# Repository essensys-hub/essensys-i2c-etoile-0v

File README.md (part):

# essensys-i2c-etoile-0v – carte N2 « étoile 0 V » sur rail DIN

Carte qui relie le boîtier principal (BP, carte SC944D) aux boîtiers auxiliaires (BA1 SC940D, BA2 SC941C,
BA3 SC942C) d'une installation Essensys **en étoile** autour d'un plan 0 V commun, à la place du chaînage d'origine.
Depuis la révision B, elle porte aussi un module ESP32 qui écoute le bus sans pouvoir y émettre, surveille ses
tensions, horodate les surtensions et gère une alarme intrusion sur batterie (voir [Révision B](#révision-b--module-esp32-espion-et-alarme)).

## Contexte : foudre 2026

Un coup de foudre indirect (août 2026) a détruit des étages I2C entre le BP et les BA : la surtension induite fait
circuler un courant d'équilibrage dans le 0 V du chaînage BP → BA1 → BA2 → BA3, et les écrêteurs des lignes SDA/SCL
conduisent dès que la chute de tension sur ce 0 V devient trop forte. Analyse et retour d'expérience :
[synthèse RETEX foudre 2026](https://www.essensys.fr/docs/retex/foudre-2026/synthese/).

N2 est la mesure « court terme » côté câblage : raccourcir et doubler les chemins 0 V, isoler chaque BA (cavalier, PTC, TVS).

- Change OpenSpec : [`i2c-surge-protection-2026-10-007`](https://github.com/essensys-hub/essensys-board-SC944D/tree/feat/i2c-surge-protection-2026-10-007/openspec/changes/i2c-surge-protection-2026-10-007)
  dans essensys-board-SC944D, tâche 4.1 (sections D3/D4 de `design.md`, spec `aux-box-interconnect`).
- Ticket : [essensys-hub/essensys-board-SC944D#1](https://github.com/essensys-hub/essensys-board-SC944D/issues/1).

## Fonction

N2 remplace le chaînage BP → BA1 → BA2 → BA3 par une **étoile** : le bus du BP (J31) arrive sur la carte
et repart vers chaque BA par un port dédié. Le 0 V de chaque BA rejoint celui du BP par un **plan 0 V double face**,
avec deux faisceaux AWG20 par BA (J1 et J2 du BA). Le 0 V du BP est doublé par une queue de cochon AWG20
soudée sur la broche traversante J31-3. But : relever le seuil de courant d'équilibrage à partir duquel
les écrêteurs I2C conduisent (au moins 4 fois la référence, à mesurer en 4.3), et garder l'écart statique de 0 V
sous 0,05 V.

Par port BA :

- **cavalier JPn** (embase 2×3 au pas de 2,54 mm, 3 shunts) qui coupe SDA, SCL et +15 V ; le 0 V n'est jamais coupé.
  Un pont 2×3 (boîtier femelle 2×3 avec 3 boucles) permet d'ouvrir les trois lignes en une seule manœuvre ;
- **PTC Fn** (CMS 1812, 30 V au moins) sur le +15 V, **puis TVS Dn SMAJ16A** entre le +15 V du port et le 0 V.
  Une TVS en court-circuit ne fait déclencher que la PTC de son port : les autres BA restent alimentés.

Partie bus : aucun composant actif, aucun firmware, aucune retouche des BA.

## Brochage (WR-MPC3 2×2, compatible Würth 66200421122)

| Broche | Signal |
|---|---|
| 1 | SDA |
| 2 | SCL |
| 3 | 0 V |
| 4 | +15 V |

| Repère | Rôle |
|---|---|
| J1 | Entrée BP, vers J31 du BP |
| J8 | Pastille (Ø 1,25 mm) pour la queue de cochon AWG20 vers J31-3 du BP |
| J2 / J3 | BA1 SC940D, vers J1 / J2 du BA |
| J4 / J5 | BA2 SC941C, vers J1 / J2 du BA |
| J6 / J7 | BA3 SC942C, vers J1 / J2 du BA |
| JP1 / JP2 / JP3 | Cavalier du port BA1 / BA2 / BA3 (impairs côté BP, pairs côté port) |
| F1–F3, D1–D3 | PTC puis TVS du +15 V de chaque port |
| H1–H4 | Trous M3 non métallisés, **non reliés** (fixation sur support DIN isolant) |

Nets : `SDA_BP`, `SCL_BP`, `+15V_BP`, `0V` ; par port `SDA_BAn`, `SCL_BAn`, `+15V_SWn` (après cavalier), `+15V_BAn` (après PTC).

## Carte

- **235 × 68 mm** (révision B ; zone bus 110 mm à gauche, zone module à droite), FR-4 1,6 mm, 2 couches,
  **cuivre 2 oz (70 µm) demandé**, HASL, vernis vert, sérigraphie blanche. Six trous M3 non reliés.
- Plan 0 V sur les deux faces (raccord plein, sans thermique), vias de couture, liaison J31-3 → pastille J8 en piste de 3 mm.
- Pistes : +15 V 1,5 à 2 mm, SDA/SCL 0,5 mm ; tronc en peigne depuis J1, une descente par port.
- Support DIN : à monter sur un porte-carte DIN **isolant** (profilé plastique pour carte de 68 mm, ou entretoises nylon M3 sur adaptateur DIN). Les trous de fixation ne sont reliés à rien.
- Zone module : plan GND sur les deux faces, vias de couture, zone sans cuivre sous l'antenne de l'ESP32 (bord haut).
  Pistes 0,25 mm (signaux), 0,4 mm (3,3 V) et 0,6 mm (puissance), vias 0,6/0,3 mm, isolement 0,2 mm.

## Révision B : module ESP32 espion et alarme

Change OpenSpec [`n2-esp32-spy-alarm-2026-10-008`](openspec/changes/n2-esp32-spy-alarm-2026-10-008),
ticket [essensys-hub/essensys-feature-lifecycle#28](https://github.com/essensys-hub/essensys-feature-lifecycle/issues/28).
Tâches matérielles couvertes ici : 1.1, 1.2, 1.3 (conception), 2.1 et 2.2 (conception, essais sur banc à faire).
Le firmware est dans `firmware/` (autre lot du même change).

La révision B ajoute à droite de la carte une **zone module** qui observe le bus sans pouvoir agir dessus,
surveille ses tensions, horodate les surtensions et gère une alarme intrusion sur batterie.
La zone bus (révision A, à gauche) est inchangée : seuls s'y ajoutent les prises de mesure, le cavalier d'écoute
et l'alimentation de l'isolateur.

### Séparation bus / module

- Deux plans distincts : **0 V** (zone bus, x < 110,3 mm) et **GND** (zone module, x > 111,7 mm), séparés par un sillon
  de 1,4 mm repéré en sérigraphie. GND rejoint le 0 V **en un seul point**, par le net-tie NT1.
- Rien n'est relié au PE : trous M3 non métallisés, aucune borne de terre. La sérigraphie TBTS est conservée
  sur les deux faces (« 0 V TBTS – NE PAS RELIER À LA TERRE », « ZONE MODULE (GND) – TBTS – AUCUNE LIAISON AU PE »).
- Seuls traversent le sillon (vérifié sur le PCB routé) : l'isolateur U1 (à cheval), NT1, le +15V_BP vers la PTC
  propre F4 du module, et les 13 lignes de mesure (MEAS_*, DA_*) **déjà limitées en courant** par leur résistance
  de prise, placée côté bus au plus près du point mesuré (150 kΩ pour les +15 V, 100 kΩ pour les prises Kelvin 0 V).

### Composants retenus

| Fonction | Repères | Référence | Remarque |
|---|---|---|---|
| MCU Wi-Fi | U6 | ESP32-C3-MINI-1-N4 | Antenne en bord de carte, zone interdite cuivre de 43 × 6,4 mm (D1) |
| Isolateur d'écoute | U1 | **ISO7720DR** (TI), 2 canaux **même sens** | Seconde source broche à broche : ADuM1200ARZ (2/0) |
| LDO côté bus de l'isolateur | U2, R3 | LP2950-5.0 (TO-92, VIN 30 V) + 100 Ω | Alimenté par +15V_BP, indépendant du module |
| Cavalier d'écoute | JP4 | Embase 2×2, 2 shunts | Retirés : aucune liaison module ↔ SDA/SCL |
| RTC | U7, C20 | RV-3028-C7 (I2C 0x52) + supercondensateur 11 mF (CPH3225A) | EVI relié au latch 0 V : horodatage matériel |
| ADC | U10–U13 | 4 × MCP3428 (16 bits, réf. interne 2,048 V, entrées différentielles) | Bus I2C local du module |
| Amplis différentiels | U9 | TLV9064 (RRIO, 10 MHz) | 3 canaux G = 0,249 + tampon VREF |
| Latch surtension | U14, U15, U16 | 2 × LM339 + 74HC74 | Réarmé par GPIO7 |
| Extension d'E/S | U8 | TCA9534 (I2C 0x20) | Latches, chargeur, clé, secteur, LED |
| PTC propre, anti-retour, TVS | F4, D4, D5 | PTC 1812 0,2 A, SS14, SMAJ16A | Défaut du module = F4 ouverte, BA alimentés |
| Abaisseur 15 → 5 V | U3, L1 | AP63205WU (5 V fixe, 3,8–32 V) + 4,7 µH | |
| Chargeur LiFePO4 | U4, TH1 | CN3058E (CC/CV 3,6 V), RISET 9,1 kΩ = 200 mA, CTN 10 kΩ B3435 | Charge autorisée ≈ 3–43 °C |
| Power-path | D6, Q1 | SS14 (secteur) + AO3401A (batterie) | Basculement sans coupure par la diode de structure de Q1 |
| LDO 3,3 V | U5 | AP2112K-3.3 | |
| Batterie | BT1, F5 | Porte-pile Keystone 1042 + IFR18650 1,5 Ah, PTC 1,5 A | |
| Entrées alarme | J10, R71–R78, D11–D14 | 4 boucles équilibrées, 1 kΩ série, SMF5.0A | FDL 2 × 4,7 kΩ |
| Clé d'armement | J11, R79, R80, D15 | Contact sec | |
| Sirène 12 V | U17, L2, D7, U18, D16 | MT3608 (boost 12 V depuis VBAT) + **BTS4140N** (high-side protégé) | Boost et sortie coupés au reset |

**Choix de l'isolateur.** L'ISO7721 et l'ADuM1201 ont un canal dans chaque sens : leur canal retour piloterait
une sortie côté bus, exactement ce que la spec interdit. Ils ne conviendraient qu'en n'utilisant qu'un canal
par boîtier (deux boîtiers, un canal retour inutilisé mais physiquement présent). L'**ISO7720** a ses deux canaux
dans le sens bus → module : côté bus il n'existe que des **entrées CMOS** (≈ 2 pF, fuite typique de quelques nA,
10 µA max en datasheet), aucune sortie. Aucune configuration logicielle ne peut donc tirer SDA ou SCL. Sa sortie
est « fail-safe haute » (niveau repos d'I2C). Le côté bus est alimenté en 5 V (niveau du bus du BP) par U2,
ce qui garde les entrées dans leur plage même quand le module est éteint.

### Raccordement firmware (ESP32-C3)

| GPIO | Net | Rôle |
|---|---|---|
| 0 | SNF_SCL | Écoute SCL (sortie OUTB de l'isolateur), entrée seule |
| 1 | SNF_SDA | Écoute SDA (OUTA), entrée seule |
| 2 | IO2 | Broche de démarrage, tirage haut 10 kΩ, libre |
| 3 | EXP_INT | /INT du TCA9534 (réveil possible) |
| 4 / 5 | I2C_SDA / I2C_SCL | Bus I2C **local** du module (4,7 kΩ), distinct du bus espionné |
| 6 | SIREN_EN | Active le boost et la sortie sirène (tirage bas 100 kΩ) |
| 7 | LATCH_RST | Réarmement des latches, actif bas (tirage haut 10 kΩ) |
| 8 | LED_STAT | LED verte, active basse (broche de démarrage, tirage haut) |
| 9 | BOOT | Bouton SW1 (démarrage / service) |
| 10 | RTC_INT | /INT du RV-3028 |
| 18 / 19 | USB_DM / USB_DP | Débogage USB (J9) |
| 20 / 21 | U0RX / U0TX | Débogage UART (J9) |

TCA9534 (0x20) : P0 LATCH_0V, P1 LATCH_OV, P2 /CHRG, P3 /DONE, P4 ARM_IN (bas = clé fermée),
P5 PG_5V (haut = secteur présent), P6 LED rouge (active basse), P7 libre (tirée bas).

MCP3428 (adresses selon la table de la datasheet, à confirmer par un scan I2C au banc, plage 0x68–0x6F) :

| Repère | Adr0 / Adr1 | CH1 | CH2 | CH3 | CH4 |
|---|---|---|---|---|---|
| U10 | 0 / 0 | +15V_BP | +15V_SW1 (amont PTC F1) | +15V_SW2 | +15V_SW3 |
| U11 | 1 / 0 | +15V_BA1 (aval PTC F1) | +15V_BA2 | +15V_BA3 | VBAT (÷ 2) |
| U12 | 0 / 1 | Boucle Z1 | Z2 | Z3 | Z4 |
| U13 | 1 / 1 | Écart 0 V port BA1 (CH− = VREF) | BA2 | BA3 | Sortie sirène (÷ 11) |

Le RV-3028 doit être configuré par le firmware : chargeur d'entretien (trickle) activé vers VBACKUP,
basculement automatique sur VBACKUP, entrée EVI sur front montant (horodatage du latch « écart de 0 V »).

### Tolérances des chaînes de mesure (tâche 1.2)

Hypothèses : résistances de mesure 0,1 % 25 ppm/°C, échauffement de 30 °C, MCP3428 à 15 éch./s
(16 bits, LSB 62,5 µV, erreur de gain 0,35 % max, offset 15 µV, réf. 15 ppm/°C), TLV9064 offset 1,6 mV max,
LM339 offset 5 mV max. « Pire cas » = somme des erreurs maximales ; « RSS » = somme quadratique.
La colonne « Résolution » suppose le mode 16 bits ; en 12 bits (240 éch./s, mode choisi par le firmware)
elle devient 16 mV sur les +15 V, 2 mV sur VBAT et 4 mV sur l'écart de 0 V, sans changer les erreurs de gain.

| Chaîne | Rapport, pleine échelle | Résolution | Pire cas | RSS | Remarque |
|---|---|---|---|---|---|
| +15 V amont/aval des PTC (7 canaux) | 10 k / (150 k + 10 k) = 1/16 ; 32,8 V | 1,0 mV | ± 0,72 % (± 0,11 V à 15 V) | ± 0,43 % (± 0,07 V) | Charge de l'ADC (2,25 MΩ) : − 0,42 % systématique, corrigée par le firmware ; sans correction ± 1,14 % (± 0,17 V) |
| VBAT | 1/2 ; 4,1 V | 0,13 mV | ± 0,9 % (± 32 mV à 3,6 V) | ± 0,6 % | Charge de l'ADC − 2,2 % systématique, corrigée ; seuil « batterie faible » 3,0 V |
| Écart de 0 V (3 canaux) | G = 24,9 k / 100 k = 0,249 ; − 4,0 V … + 8,2 V | 0,25 mV | ± (8 mV + 0,6 % de la lecture) | ± (4 mV + 0,4 %) | Offset dominé par le TLV9064 ; avec un zéro mesuré à la mise en service : ± (1 mV + 0,6 %). Objectif 4.3 (≤ 0,05 V) mesurable |
| Seuil du latch « écart de 0 V » | ± 1,00 V (fenêtre VREF ± 0,249 V) | – | ± 0,06 V | ± 0,03 V | Comparateurs ± 32 mV, ampli ± 8 mV, tampon VREF ± 6 mV, échelle ± 12 mV ; impulsion mini ≈ 1–2 µs (onde 8/20 µs captée) |
| Seuil du latch « surtension +15 V » | 16 × 1,249 V = 20,0 V | – | ± 0,15 V | ± 0,09 V | Filtre 9,4 kΩ / 100 pF (τ ≈ 0,9 µs) ; impulsion mini ≈ 2 µs |
| Boucles d'alarme | 3,3 V, 10 kΩ + 1 kΩ série | 0,06 mV | ± 4 % par état | – | FDL 5 %, 3,3 V ± 2 %, voir les seuils ci-dessous |
| Sortie sirène | 1/11 ; 22,5 V | 0,7 mV | ± 0,7 % | – | Détection de court-circuit (sortie < 6 V sirène active) |

Boucles équilibrées (FDL 4,7 kΩ en série avec le contact + 4,7 kΩ en parallèle) :

| État | Résistance de boucle | Tension mesurée | Seuils proposés |
|---|---|---|---|
| Court-circuit (sabotage) | 0 Ω | 0,30 V | < 0,75 V |
| Repos (fermée) | 4,7 kΩ | 1,20 V (1,15–1,25) | 0,75–1,44 V |
| Alarme (ouverte) | 9,4 kΩ | 1,68 V (1,61–1,75) | 1,44–1,95 V |
| Coupée (sabotage) | ∞ | saturation (≥ 2,047 V) | > 1,95 V |

Détection « PTC déclenchée » : aval < 2 V alors que l'amont est > 12 V (une PTC déclenchée laisse
quelques volts au plus). La chute normale dans une PTC (≈ 0,05 à 0,2 V) est du même ordre que l'erreur de deux
canaux : le module ne mesure pas le courant des départs, il détecte le déclenchement.

### Budget de consommation (calcul, mesure en tâche 2.3)

Charges du rail 3,3 V (moyennes) : ESP32-C3 Wi-Fi en économie et décodage I2C actif ≈ 40 mA (crête 350 mA
en émission), analogique et logique ≈ 7,8 mA (TLV9064 2,2 mA, 2 × LM339 1,6 mA, ISO7720 côté module
1,2 mA, 4 × MCP3428 0,6 mA, 4 boucles au repos 0,84 mA, LED 1,3 mA, échelle de seuils 0,1 mA).

| Cas (sur +15 V, rendement de l'abaisseur 85 %) | 5 V | +15 V |
|---|---|---|
| Batterie pleine, Wi-Fi en économie | 48 mA | 19 mA |
| **Batterie vide** (charge 200 mA) + Wi-Fi en économie | 248 mA | **97 mA** |
| Batterie vide + émission Wi-Fi (crête de quelques ms) | 560 mA | 220 mA |
| Côté bus : LP2950 + isolateur + 7 diviseurs de mesure | – | 2,3 mA |
| **Total pire cas en régime établi** | | **≈ 100 mA (1,5 W)** |

- La sirène est alimentée par **VBAT** (boost MT3608) et non par le +15 V : 12 V × 0,2 A ≈ 0,9 A sur la batterie
  pendant 3 min au plus (≈ 44 mAh), sans effet sur le +15 V du bus.
- F4 (Ihold 0,2 A à 23 °C, ≈ 0,16 A à 50 °C) tient les 100 mA établis ; les crêtes Wi-Fi de quelques ms
  ne la font pas déclencher (constante thermique de l'ordre de la seconde).
- Le +15 V du BP doit fournir ces ≈ 100 mA **en plus** des BA : à reporter dans le dimensionnement
  PTC ≥ 1,5 × BA_ALIM (design D7), vérification en 2.3.

Autonomie sur batterie (1,5 Ah, 80 % utilisables = 1,2 Ah ; sur batterie le BP a coupé le +15 V,
il n'y a plus de trafic I2C à décoder) :

| Profil firmware | Courant moyen | Autonomie |
|---|---|---|
| Wi-Fi actif en permanence (≈ 80 mA) | 88 mA | 14 h |
| Wi-Fi en économie, CPU actif (≈ 40 mA) | 48 mA | 25 h |
| Veille légère + DTIM, alarme armée (≈ 10 mA) | 18 mA | 67 h |

L'objectif de 24 h (tâche 5.4) suppose un firmware en économie d'énergie sur batterie (≤ 50 mA en moyenne).

## Fichiers

| Fichier | Contenu |
|---|---|
| `n2-etoile-0v.kicad_pro/.kicad_sch/.kicad_pcb` | Projet KiCad 9 |
| `n2-etoile-0v.kicad_sym`, `sym-lib-table`, `fp-lib-table` | Symboles propres (ESP32-C3-MINI-1, CN3058E) et tables de bibliothèques du projet |
| `export/n2-etoile-0v-schema.pdf` | Schéma |
| `export/n2-etoile-0v-bom.csv` | BOM |
| `export/n2-etoile-0v-gerber.zip` | Gerber, perçages Excellon, plan de perçage, job Gerber |
| `export/n2-etoile-0v-pcb-{top,bottom}.{png,svg}` | Rendus 3D et tracés cuivre |
| `rapports/erc.rpt`, `rapports/drc.rpt` | ERC et DRC (avec parité schéma) : 0 erreur, 0 avertissement |
| `scripts/` | Générateurs Python et `build.sh` : `n2_module.py` (composants et nets du module, source unique), `gen_sch.py`, `gen_pcb.py` (placement), `autoroute.py` (routeur maillé déterministe avec arrachage ciblé et réparation des plans), `fill_zones.py` |

## Régénérer

Prérequis : KiCad 9 installé dans `/Applications/KiCad` (macOS ; adapter `KC` et `KP` dans `scripts/build.sh` sinon).

```sh
sh scripts/build.sh
```

Le script régénère schéma et PCB (le routage du module prend environ 5 minutes), relance ERC et DRC
(avec parité schéma), refait tous les exports et échoue si ERC ou DRC signalent une erreur.
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
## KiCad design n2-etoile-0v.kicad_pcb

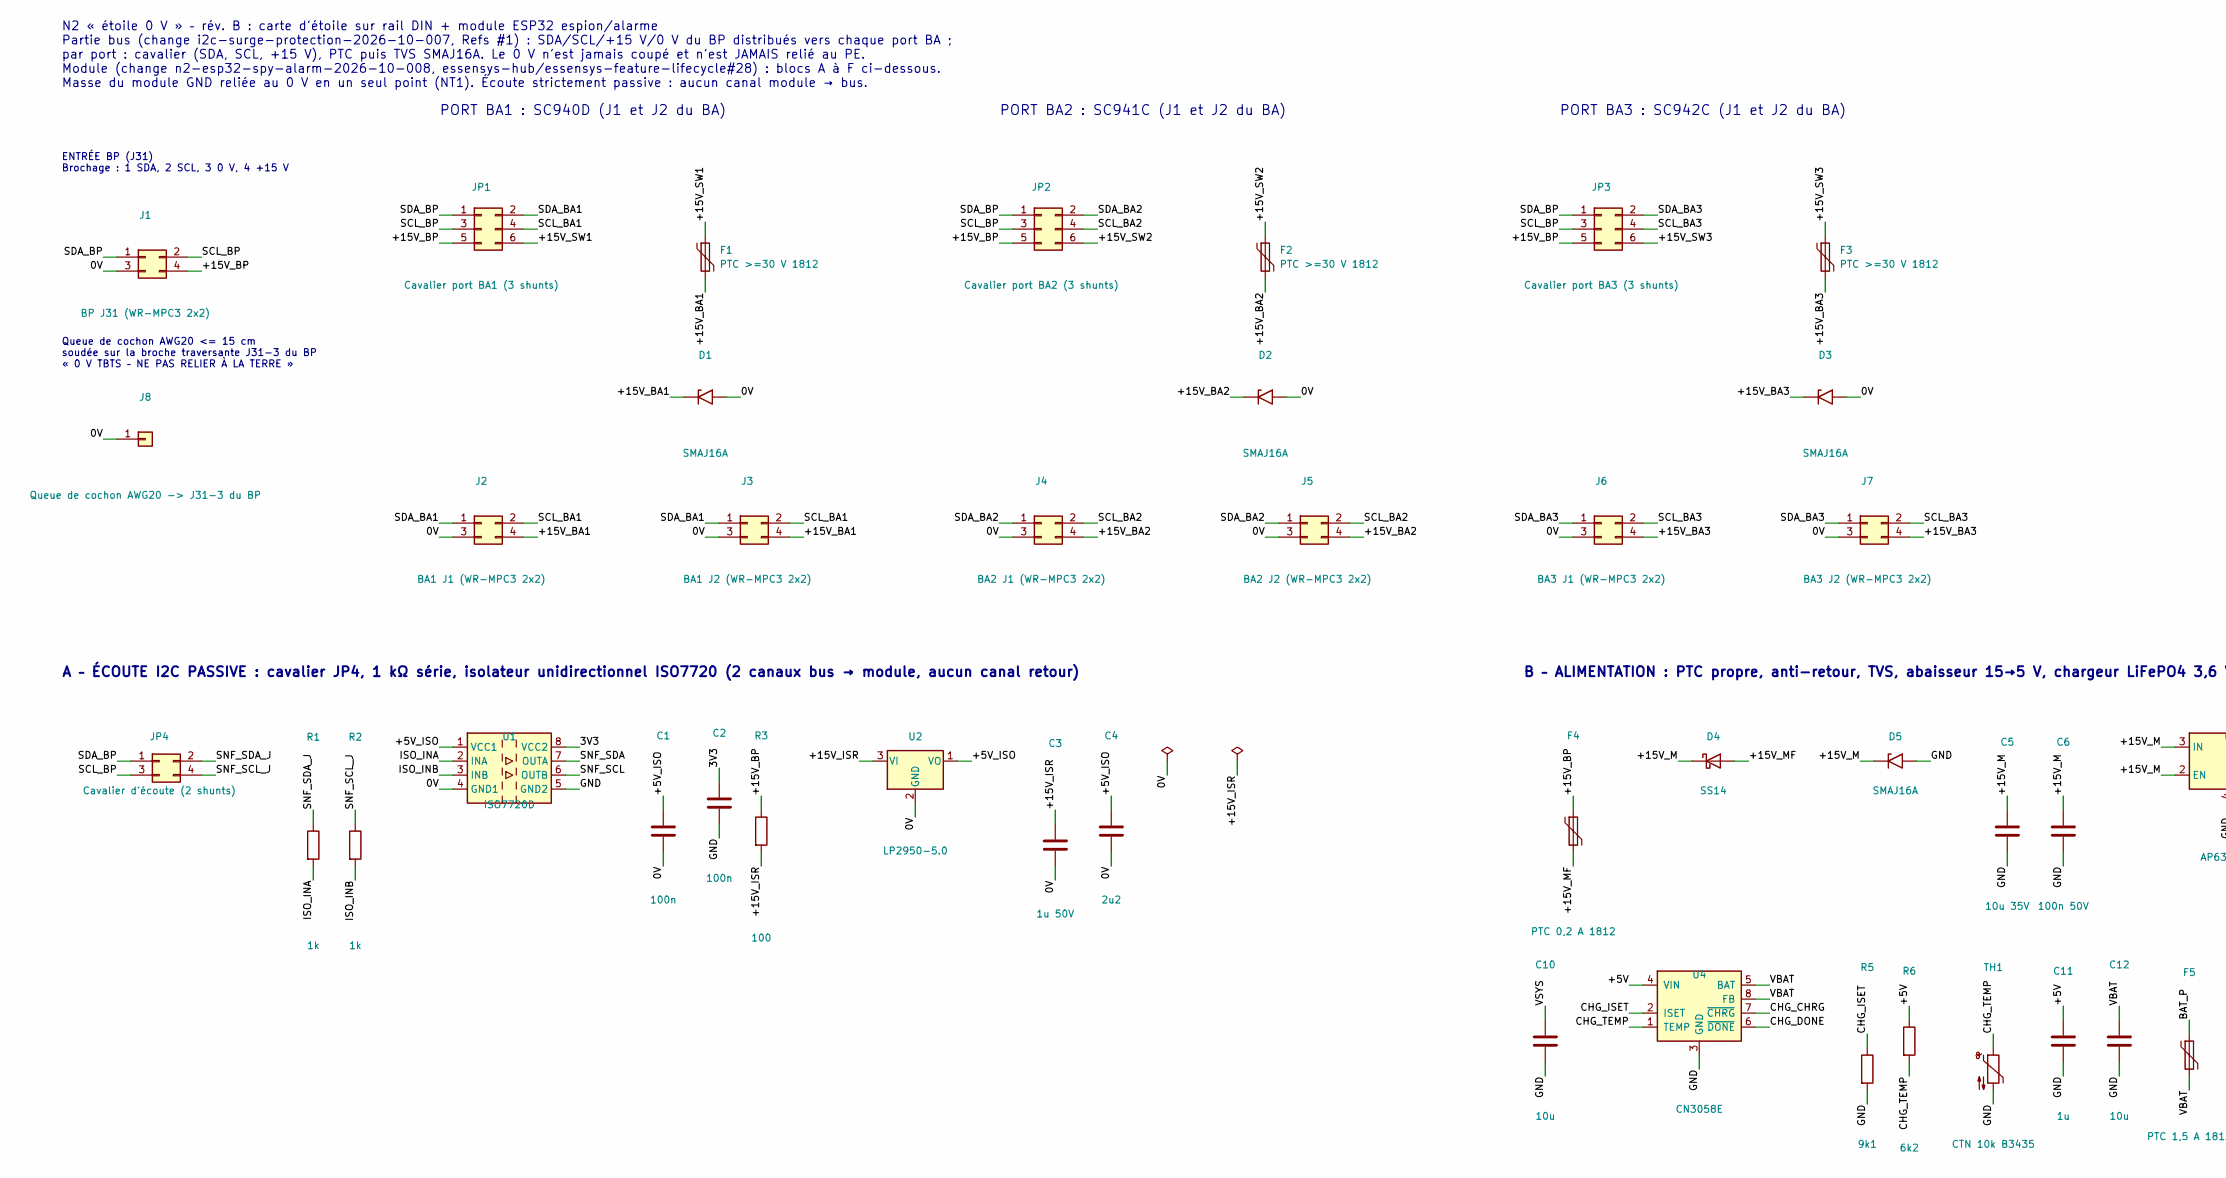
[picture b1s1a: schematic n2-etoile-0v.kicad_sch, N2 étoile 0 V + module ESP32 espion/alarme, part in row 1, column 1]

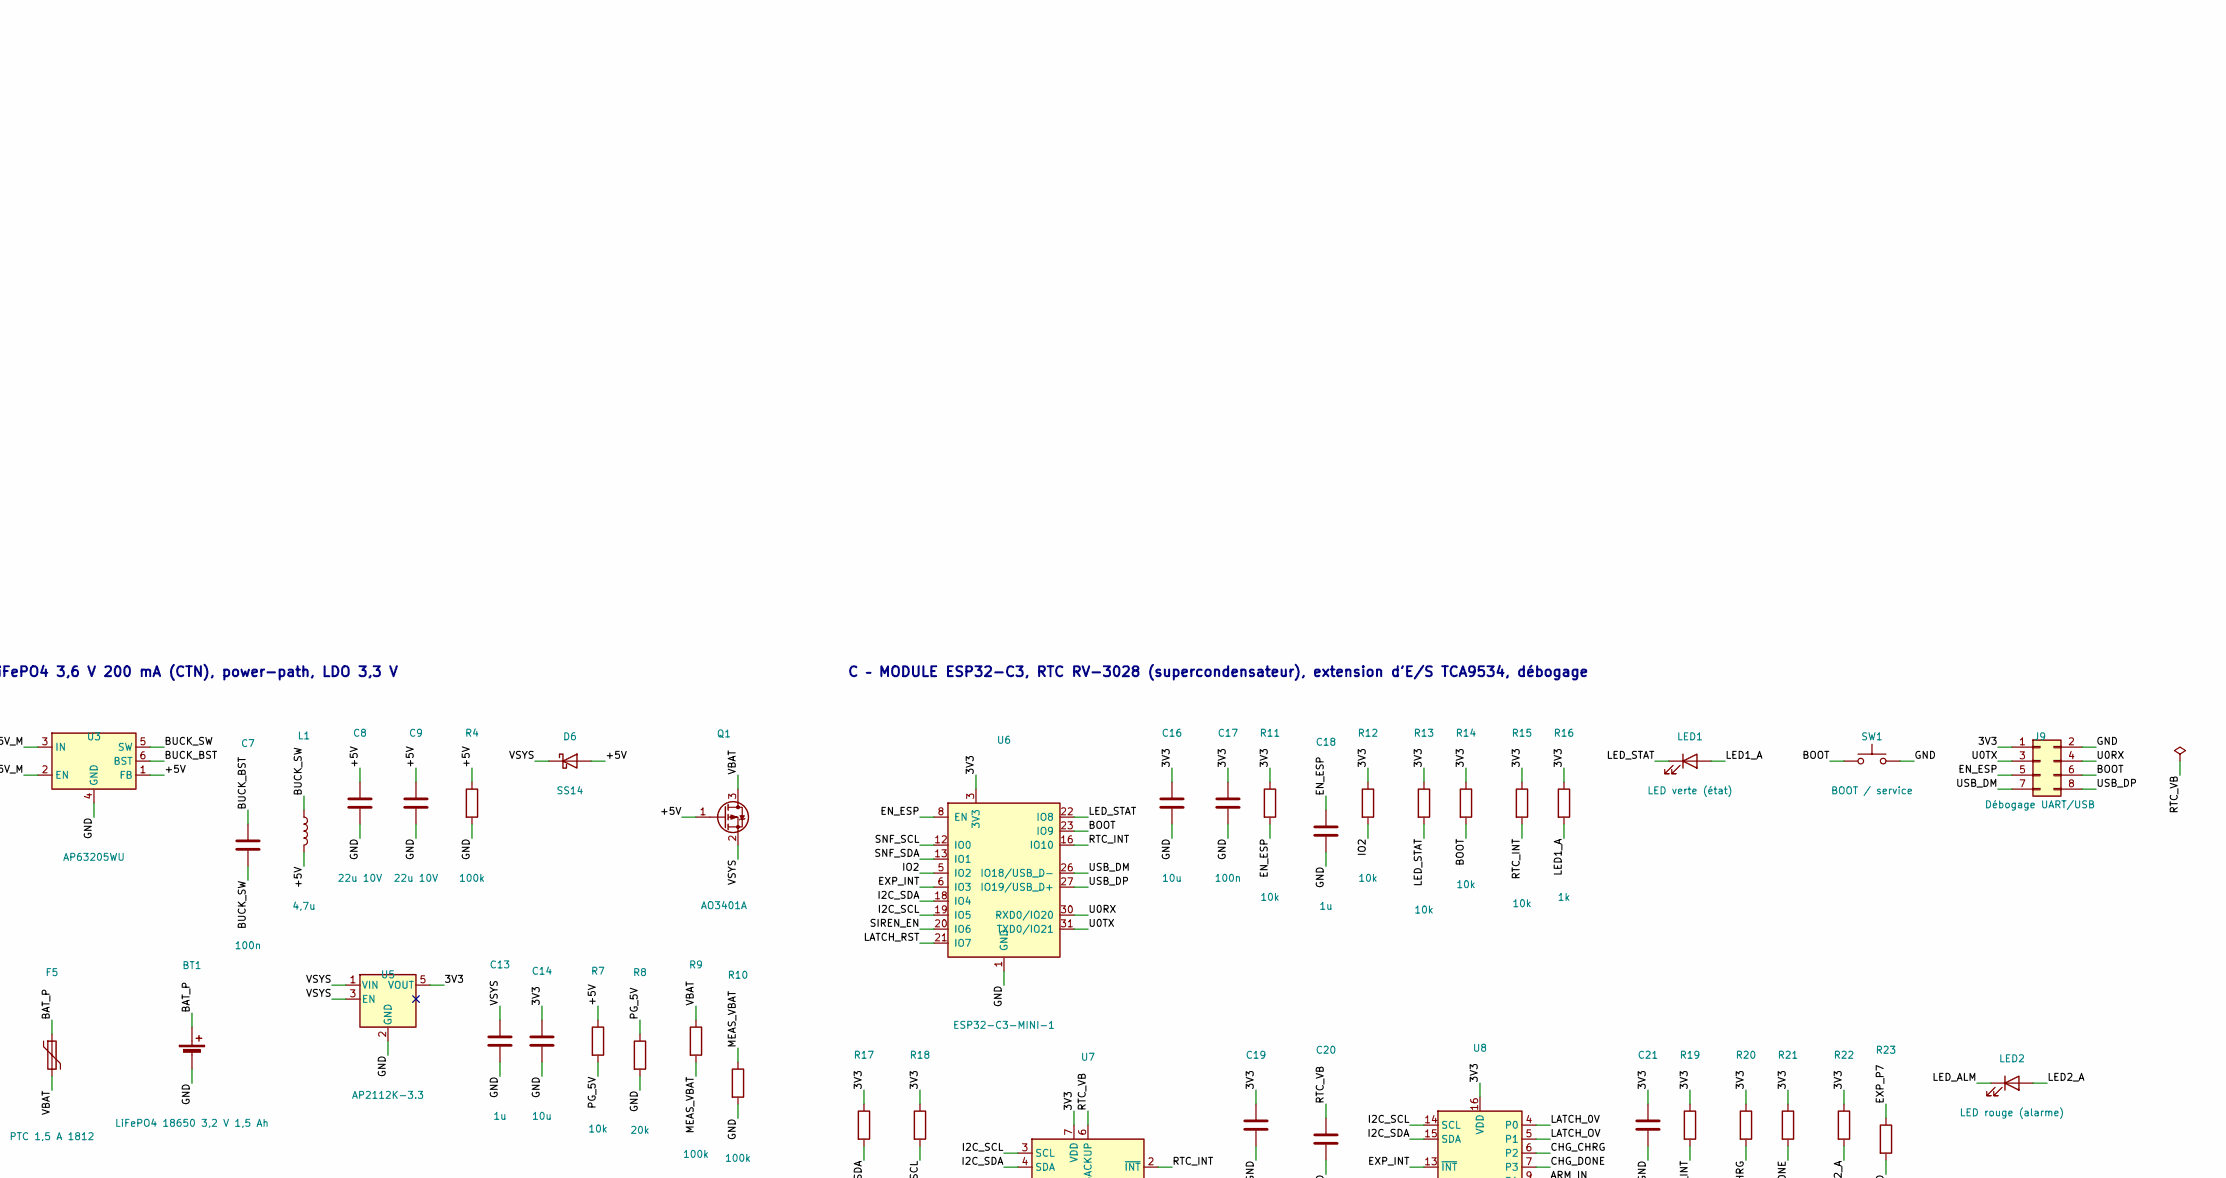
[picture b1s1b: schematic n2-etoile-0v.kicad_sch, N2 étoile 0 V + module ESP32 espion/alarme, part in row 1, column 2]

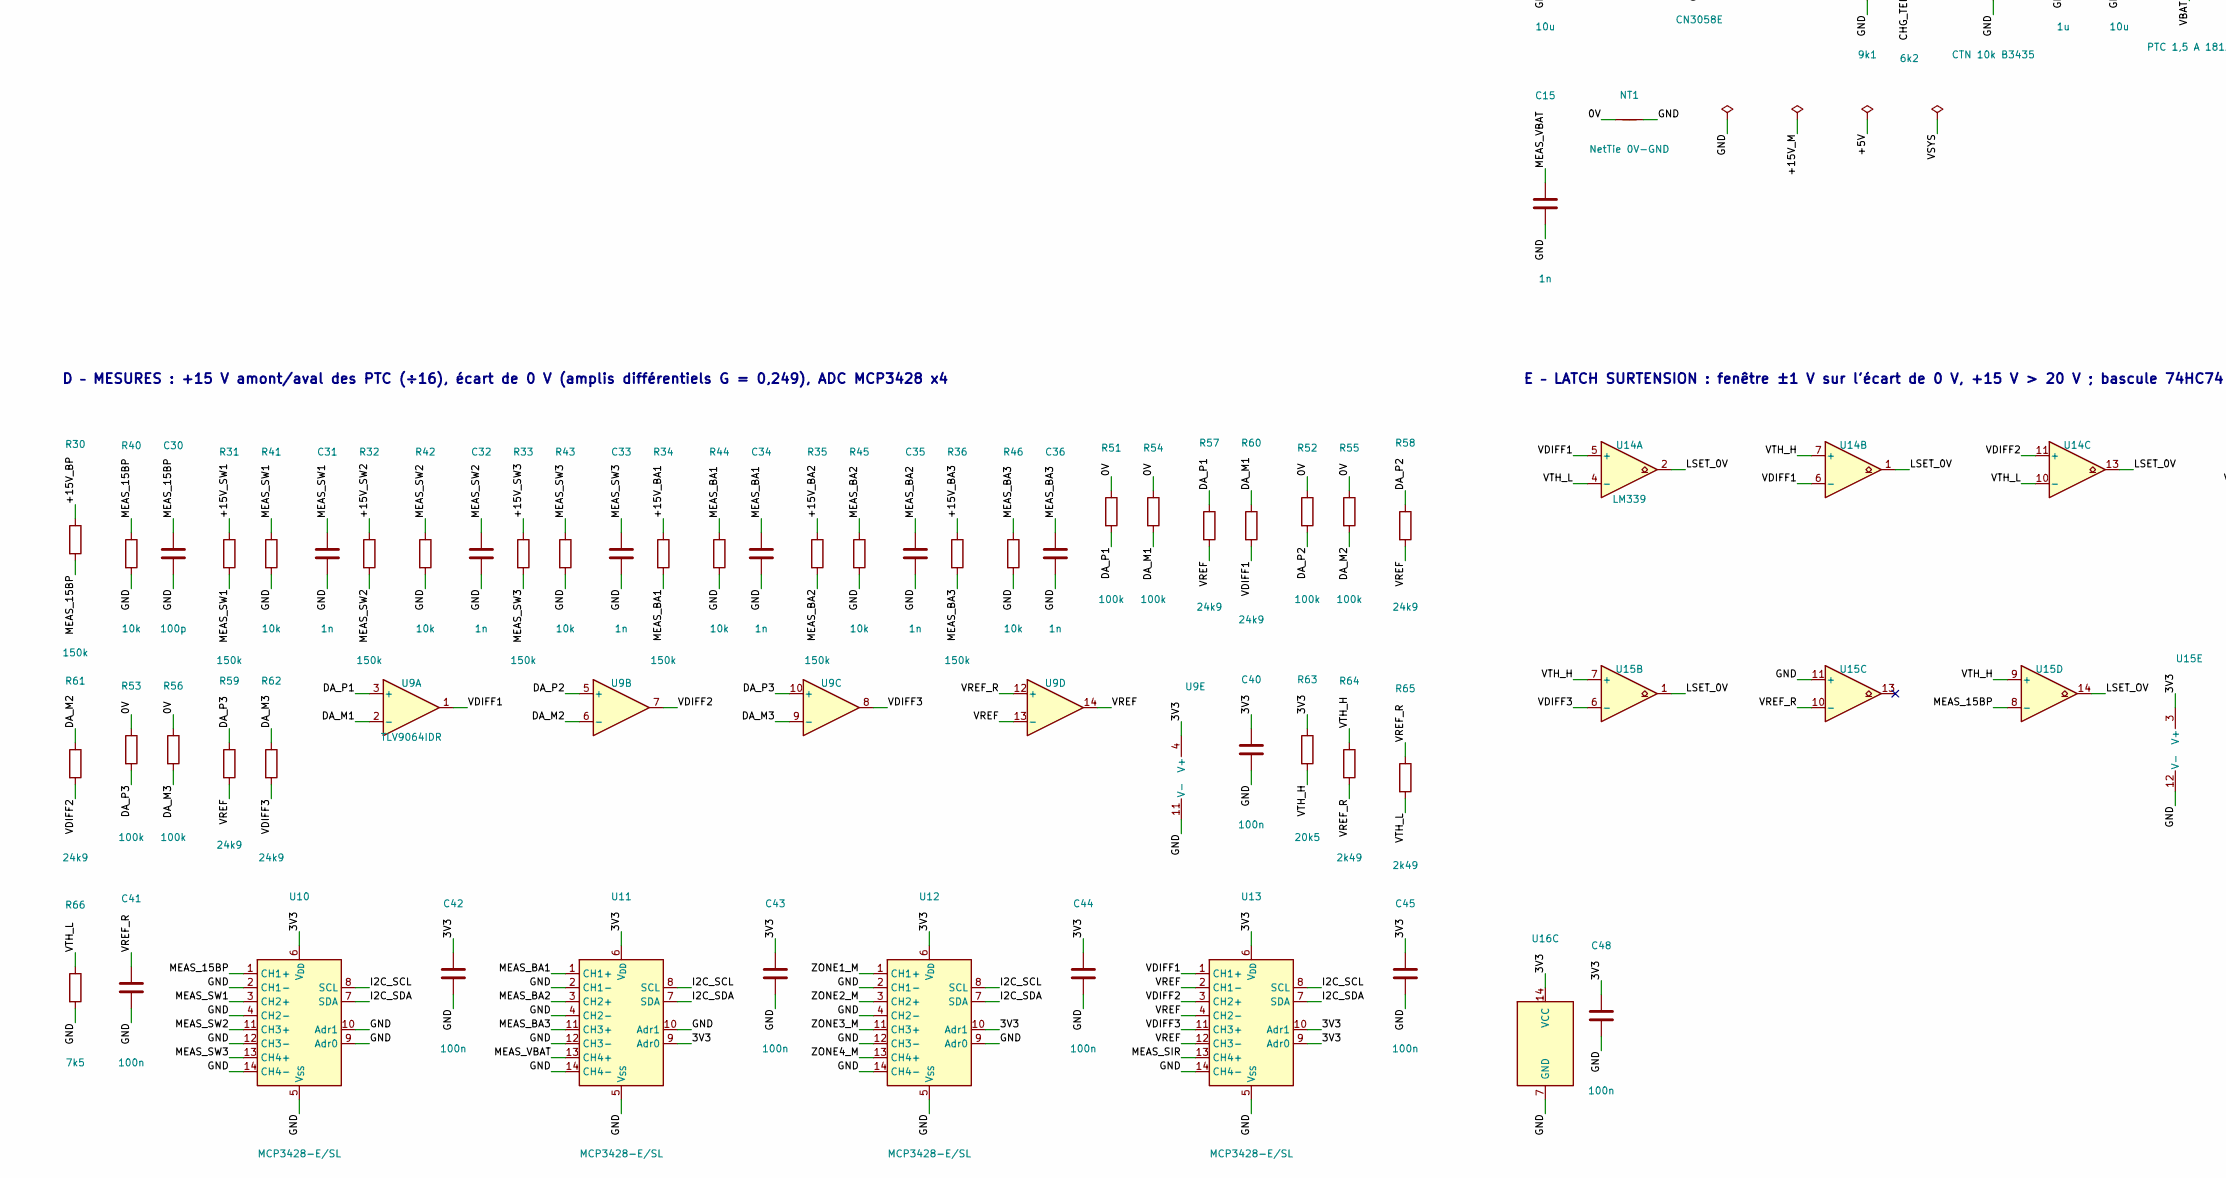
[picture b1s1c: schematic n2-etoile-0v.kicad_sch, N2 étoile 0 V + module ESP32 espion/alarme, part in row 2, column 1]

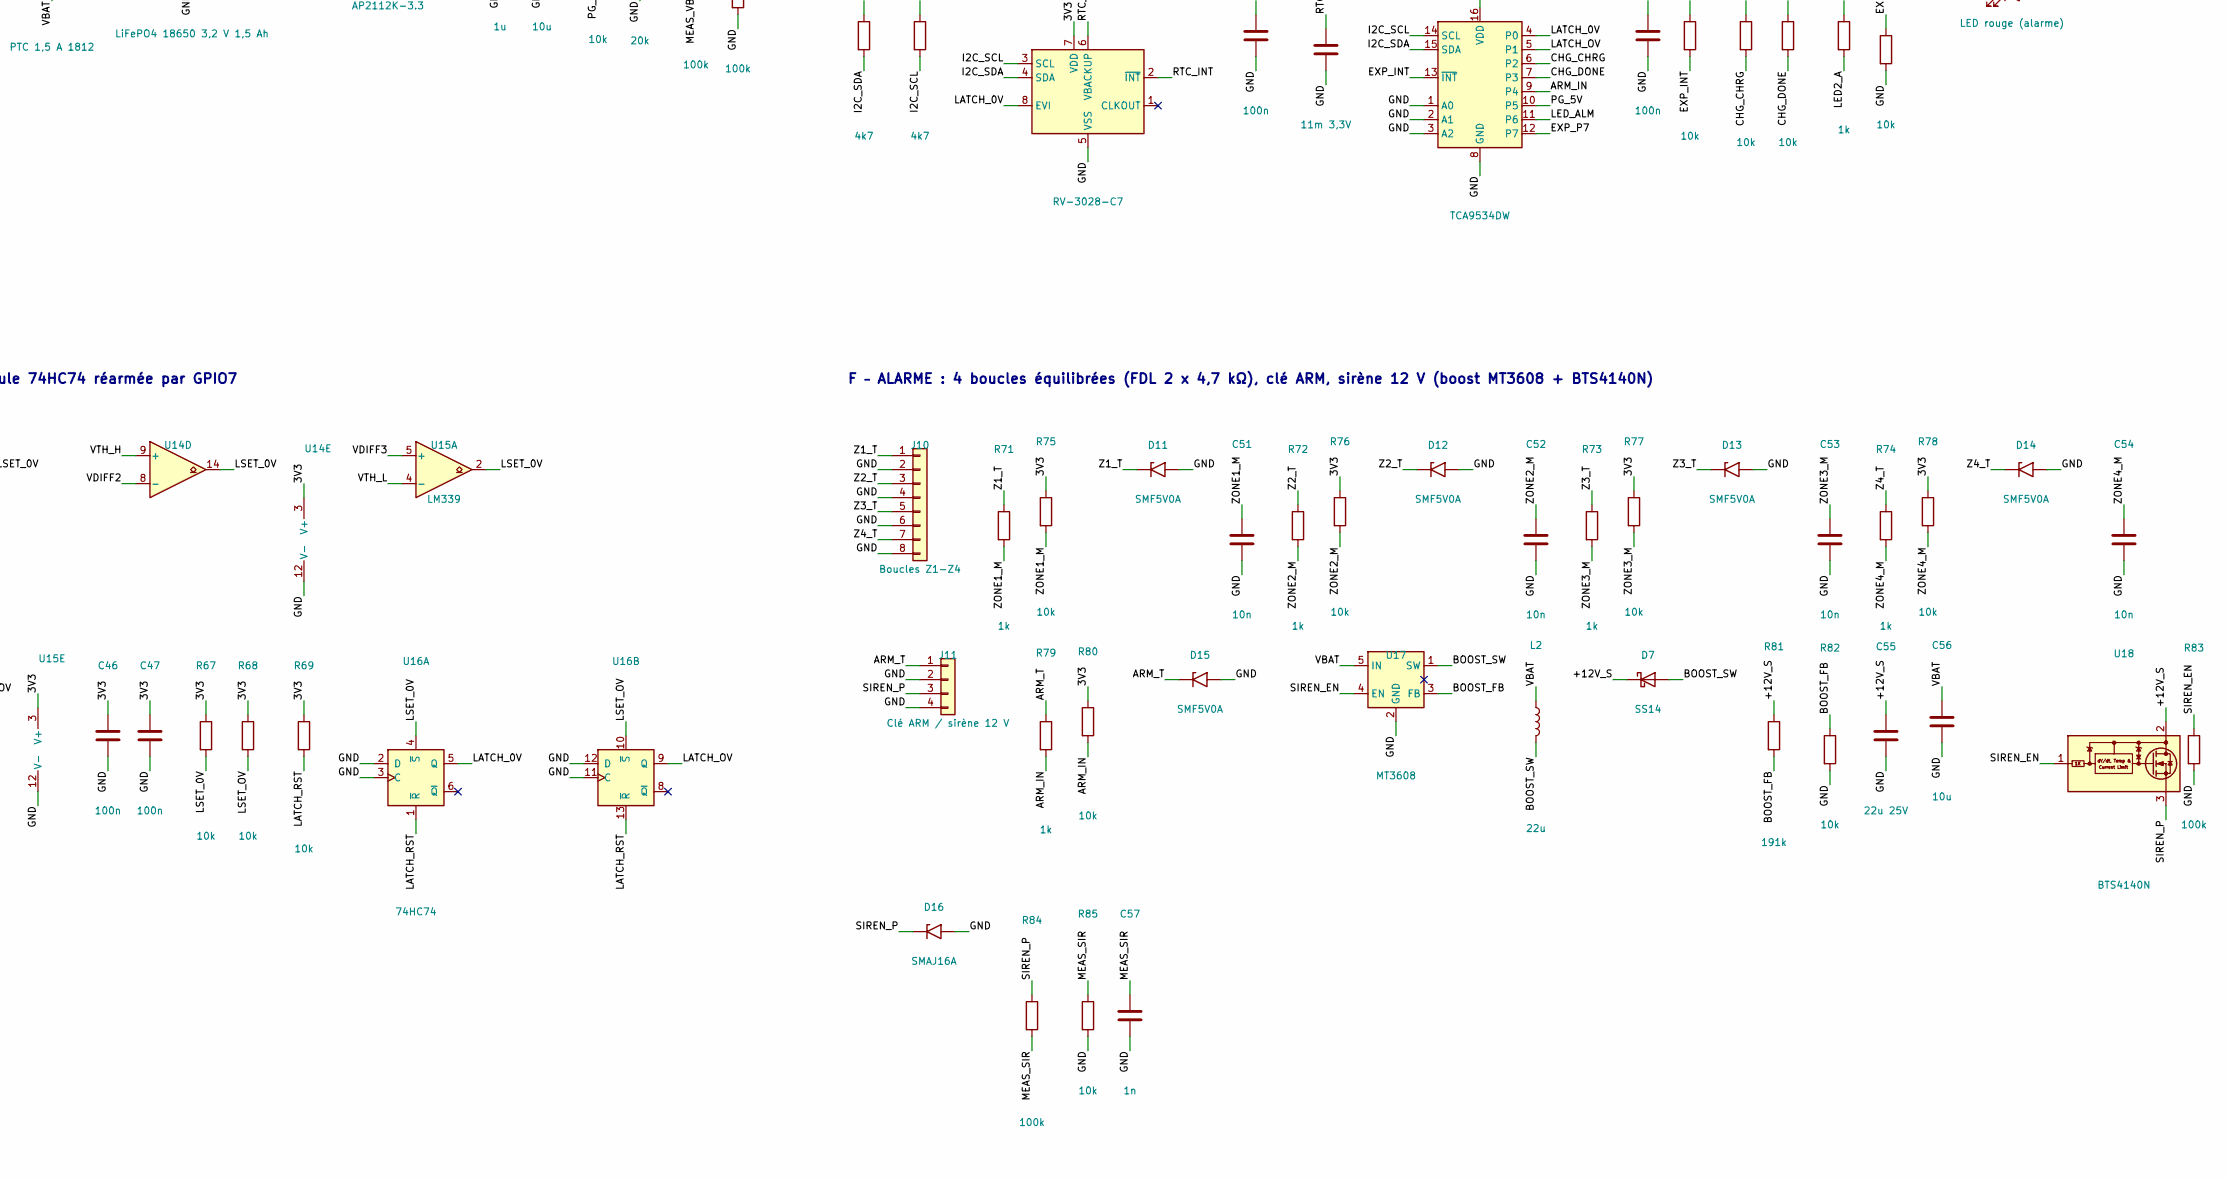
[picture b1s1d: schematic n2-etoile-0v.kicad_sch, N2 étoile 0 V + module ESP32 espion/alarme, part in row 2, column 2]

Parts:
BT1: LiFePO4 18650 3,2 V 1,5 Ah; BatteryHolder_Keystone_1042_1x18650; MPN 1042 (porte-pile 18650) + cellule IFR18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
C1, C2, C7, C17, C19, C21, C40, C41, C42, C43, C44, C45, C46, C47, C48: 100n; C_0603_1608Metric
C3: 1u 50V; C_0805_2012Metric
C4: 2u2; C_0603_1608Metric
C5: 10u 35V; C_1206_3216Metric
C6: 100n 50V; C_0603_1608Metric
C8, C9: 22u 10V; C_1206_3216Metric
C10, C12, C14, C16, C56: 10u; C_0805_2012Metric
C11, C13, C18: 1u; C_0603_1608Metric
C15, C31, C32, C33, C34, C35, C36, C57: 1n; C_0603_1608Metric
C20: 11m 3,3V; C_1210_3225Metric; MPN CPH3225A (supercondensateur, chargé par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
C30: 100p; C_0603_1608Metric
C51, C52, C53, C54: 10n; C_0603_1608Metric
C55: 22u 25V; C_1206_3216Metric
D1, D2, D3, D5, D16: SMAJ16A; D_SMA; MPN SMAJ16A
D4, D6, D7: SS14; D_SMA
D11, D12, D13, D14, D15: SMF5V0A; D_SMF; MPN SMF5.0A
F1, F2, F3: PTC >=30 V 1812; Fuse_1812_4532Metric; MPN 1812L050/30MR (à confirmer : Ihold@50°C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
F4: PTC 0,2 A 1812; Fuse_1812_4532Metric; MPN MF-MSMF020-2 (Ihold 0,2 A, 30 V, à conf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
F5: PTC 1,5 A 1812; Fuse_1812_4532Metric; MPN 1812L150/12MR (à confirmer)
J1: BP J31 (WR-MPC3 2x2); Molex_Micro-Fit_3.0_43045-0412_2x02_P3.00mm_Vertical; MPN 66200421122 (WR-MPC3 2x2, vertical, THT)
J2: BA1 J1 (WR-MPC3 2x2); Molex_Micro-Fit_3.0_43045-0412_2x02_P3.00mm_Vertical; MPN 66200421122 (WR-MPC3 2x2, vertical, THT)
J3: BA1 J2 (WR-MPC3 2x2); Molex_Micro-Fit_3.0_43045-0412_2x02_P3.00mm_Vertical; MPN 66200421122 (WR-MPC3 2x2, vertical, THT)
J4: BA2 J1 (WR-MPC3 2x2); Molex_Micro-Fit_3.0_43045-0412_2x02_P3.00mm_Vertical; MPN 66200421122 (WR-MPC3 2x2, vertical, THT)
J5: BA2 J2 (WR-MPC3 2x2); Molex_Micro-Fit_3.0_43045-0412_2x02_P3.00mm_Vertical; MPN 66200421122 (WR-MPC3 2x2, vertical, THT)
J6: BA3 J1 (WR-MPC3 2x2); Molex_Micro-Fit_3.0_43045-0412_2x02_P3.00mm_Vertical; MPN 66200421122 (WR-MPC3 2x2, vertical, THT)
J7: BA3 J2 (WR-MPC3 2x2); Molex_Micro-Fit_3.0_43045-0412_2x02_P3.00mm_Vertical; MPN 66200421122 (WR-MPC3 2x2, vertical, THT)
J8: Queue de cochon AWG20 -> J31-3 du BP; SolderWire-0.75sqmm_1x01_D1.25mm_OD3.5mm
J9: Débogage UART/USB; PinHeader_2x04_P2.54mm_Vertical
J10: Boucles Z1-Z4; TerminalBlock_Phoenix_PT-1,5-8-3.5-H_1x08_P3.50mm_Horizontal; MPN 1984688 (PT 1,5/8-3,5-H)
J11: Clé ARM / sirène 12 V; TerminalBlock_Phoenix_PT-1,5-4-3.5-H_1x04_P3.50mm_Horizontal; MPN 1984633 (PT 1,5/4-3,5-H)
JP1: Cavalier port BA1 (3 shunts); PinHeader_2x03_P2.54mm_Vertical
JP2: Cavalier port BA2 (3 shunts); PinHeader_2x03_P2.54mm_Vertical
JP3: Cavalier port BA3 (3 shunts); PinHeader_2x03_P2.54mm_Vertical
JP4: Cavalier d'écoute (2 shunts); PinHeader_2x02_P2.54mm_Vertical
L1: 4,7u; L_Taiyo-Yuden_NR-40xx; MPN NR4018T4R7M
L2: 22u; L_Taiyo-Yuden_NR-50xx; MPN NR5040T220M
LED1: LED verte (état); LED_0603_1608Metric
LED2: LED rouge (alarme); LED_0603_1608Metric
NT1: NetTie 0V-GND; NetTie-2_SMD_Pad2.0mm
Q1: AO3401A; SOT-23
R1, R2, R16, R22: 1k; R_0603_1608Metric
R3: 100; R_1206_3216Metric
R4, R83: 100k; R_0603_1608Metric
R5: 9k1; R_0603_1608Metric
R6: 6k2; R_0603_1608Metric
R7, R11, R12, R13, R14, R15, R19, R20, R21, R23, R67, R68, R69, R75, R76, R77, R78, R80, R82: 10k; R_0603_1608Metric
R8: 20k; R_0603_1608Metric
R9, R10, R84: 100k; R_0603_1608Metric; Tolerance 0,1 % 25 ppm/°C
R17, R18: 4k7; R_0603_1608Metric
R30, R31, R32, R33, R34, R35, R36: 150k; R_0805_2012Metric; Tolerance 0,1 % 25 ppm/°C
R40, R41, R42, R43, R44, R45, R46, R85: 10k; R_0603_1608Metric; Tolerance 0,1 % 25 ppm/°C
R51, R52, R53, R54, R55, R56: 100k; R_1206_3216Metric; Tolerance 0,1 % 25 ppm/°C
R57, R58, R59, R60, R61, R62: 24k9; R_0603_1608Metric; Tolerance 0,1 % 25 ppm/°C
R63: 20k5; R_0603_1608Metric; Tolerance 0,1 % 25 ppm/°C
R64, R65: 2k49; R_0603_1608Metric; Tolerance 0,1 % 25 ppm/°C
R66: 7k5; R_0603_1608Metric; Tolerance 0,1 % 25 ppm/°C
R71, R72, R73, R74, R79: 1k; R_0805_2012Metric
R81: 191k; R_0603_1608Metric
SW1: BOOT / service; SW_SPST_PTS645Sx43SMTR92
TH1: CTN 10k B3435; R_0603_1608Metric; MPN NCP18XH103F03RB (au contact du porte-pi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
U1: ISO7720D; SOIC-8_3.9x4.9mm_P1.27mm; MPN ISO7720DR (2/0 canaux ; seconde source 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
U2: LP2950-5.0; TO-92_Inline; MPN LP2950-50LPRE3 (VIN max 30 V)
U3: AP63205WU; TSOT-23-6; MPN AP63205WU-7 (5 V fixe, 3,8-32 V)
U4: CN3058E; SOIC-8-1EP_3.9x4.9mm_P1.27mm_EP2.41x3.3mm; MPN CN3058E (LiFePO4 3,6 V ; brochage à vér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
U5: AP2112K-3.3; SOT-23-5; MPN AP2112K-3.3TRG1
U6: ESP32-C3-MINI-1; ESP32-C6-MINI-1; MPN ESP32-C3-MINI-1-N4 (empreinte = motif M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
U7: RV-3028-C7; MicroCrystal_C7_SON-8_1.5x3.2mm_P0.9mm; MPN RV-3028-C7 32.768kHz 1ppm-TA-QC (I2C 0x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
U8: TCA9534DW; SOIC-16W_7.5x10.3mm_P1.27mm; MPN TCA9534DWR (I2C 0x20)
U9: TLV9064IDR; SOIC-14_3.9x8.7mm_P1.27mm; MPN TLV9064IDR (10 MHz, RRIO)
U10, U11, U12, U13: MCP3428-E/SL; SOIC-14_3.9x8.7mm_P1.27mm; MPN MCP3428-E/SL (16 bits, réf. 2,048 V ; A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
U14: LM339; SOIC-14_3.9x8.7mm_P1.27mm; MPN LM339DR
U15: LM339; SOIC-14_3.9x8.7mm_P1.27mm; MPN LM339DR (U15D inutilisé)
U16: 74HC74; SOIC-14_3.9x8.7mm_P1.27mm; MPN 74HC74D
U17: MT3608; SOT-23-6; MPN MT3608 (12 V depuis VBAT, actif seuleme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
U18: BTS4140N; SOT-223; MPN BTS4140N (high-side protégé : limitatio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

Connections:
/0V: C1.2, C3.2, C4.2, D1.2 (A2), D2.2 (A2), D3.2 (A2), J1.3, J2.3, J3.3, J4.3, J5.3, J6.3, J7.3, J8.1, NT1.1, R51.1, R52.1, R53.1, R54.1, R55.1, R56.1, U1.4 (GND1), U2.2 (GND)
/3V3: C2.1, C14.1, C16.1, C17.1, C19.1, C21.1, C40.1, C42.1, C43.1, C44.1, C45.1, C46.1, C47.1, C48.1, J9.1, R11.1, R12.1, R13.1, R14.1, R15.1, R16.1, R17.1, R18.1, R19.1, R20.1, R21.1, R22.1, R63.1, R67.1, R68.1, R69.1, R75.1, R76.1, R77.1, R78.1, R80.1, U1.8 (VCC2), U5.5 (VOUT), U6.3 (3V3), U7.7 (VDD), U8.16 (VDD), U9.4 (V+), U10.6 (V_{DD}), U11.6 (V_{DD}), U11.9 (Adr0), U12.6 (V_{DD}), U12.10 (Adr1), U13.6 (V_{DD}), U13.9 (Adr0), U13.10 (Adr1), U14.3 (V+), U15.3 (V+), U16.14 (VCC)
/+5V: C8.1, C9.1, C11.1, D6.2 (A), L1.2, Q1.1 (G), R4.1, R6.1, R7.1, U3.1 (FB), U4.4 (VIN)
/+5V_ISO: C1.1, C4.1, U1.1 (VCC1), U2.1 (VO)
/+12V_S: C55.1, D7.1 (K), R81.1, U18.2 (V_{bb}), U18.4 (V_{bb})
/+15V_BA1: D1.1 (A1), F1.2, J2.4, J3.4, R34.1
/+15V_BA2: D2.1 (A1), F2.2, J4.4, J5.4, R35.1
/+15V_BA3: D3.1 (A1), F3.2, J6.4, J7.4, R36.1
/+15V_BP: F4.1, J1.4, JP1.5, JP2.5, JP3.5, R3.1, R30.1
/+15V_ISR: C3.1, R3.2, U2.3 (VI)
/+15V_M: C5.1, C6.1, D4.1 (K), D5.1 (A1), U3.2 (EN), U3.3 (IN)
/+15V_MF: D4.2 (A), F4.2
/+15V_SW1: F1.1, JP1.6, R31.1
/+15V_SW2: F2.1, JP2.6, R32.1
/+15V_SW3: F3.1, JP3.6, R33.1
/ARM_IN: R79.2, R80.2, U8.9 (P4)
/ARM_T: D15.1 (A1), J11.1, R79.1
/BAT_P: BT1.1 (+), F5.1
/BOOST_FB: R81.2, R82.1, U17.3 (FB)
/BOOST_SW: D7.2 (A), L2.2, U17.1 (SW)
/BOOT: J9.6, R14.2, SW1.1, U6.23 (IO9)
/BUCK_BST: C7.1, U3.6 (BST)
/BUCK_SW: C7.2, L1.1, U3.5 (SW)
/CHG_CHRG: R20.2, U4.7 (~CHRG), U8.6 (P2)
/CHG_DONE: R21.2, U4.6 (~DONE), U8.7 (P3)
/CHG_ISET: R5.1, U4.2 (ISET)
/CHG_TEMP: R6.2, TH1.1, U4.1 (TEMP)
/DA_M1: R54.2, R60.1, U9.2 (-)
/DA_M2: R55.2, R61.1, U9.6 (-)
/DA_M3: R56.2, R62.1, U9.9 (-)
/DA_P1: R51.2, R57.1, U9.3 (+)
/DA_P2: R52.2, R58.1, U9.5 (+)
/DA_P3: R53.2, R59.1, U9.10 (+)
/EN_ESP: C18.1, J9.5, R11.2, U6.8 (EN)
/EXP_INT: R19.2, U6.6 (IO3), U8.13 (~INT)
/EXP_P7: R23.1, U8.12 (P7)
/GND: BT1.2 (-), C2.2, C5.2, C6.2, C8.2, C9.2, C10.2, C11.2, C12.2, C13.2, C14.2, C15.2, C16.2, C17.2, C18.2, C19.2, C20.2, C21.2, C30.2, C31.2, C32.2, C33.2, C34.2, C35.2, C36.2, C40.2, C41.2, C42.2, C43.2, C44.2, C45.2, C46.2, C47.2, C48.2, C51.2, C52.2, C53.2, C54.2, C55.2, C56.2, C57.2, D5.2 (A2), D11.2 (A2), D12.2 (A2), D13.2 (A2), D14.2 (A2), D15.2 (A2), D16.2 (A2), J9.2, J10.2, J10.4, J10.6, J10.8, J11.2, J11.4, NT1.2, R4.2, R5.2, R8.2, R10.2, R23.2, R40.2, R41.2, R42.2, R43.2, R44.2, R45.2, R46.2, R66.2, R82.2, R83.2, R85.2, SW1.2, TH1.2, U1.5 (GND2), U3.4 (GND), U4.3 (GND), U4.9 (GND), U5.2 (GND), U6.1 (GND), U6.2 (GND), U6.11 (GND), U6.14 (GND), U6.36 (GND), U6.37 (GND), U6.38 (GND), U6.39 (GND), U6.40 (GND), U6.41 (GND), U6.42 (GND), U6.43 (GND), U6.44 (GND), U6.45 (GND), U6.46 (GND), U6.47 (GND), U6.48 (GND), U6.49 (GND), U6.50 (GND), U6.51 (GND), U6.52 (GND), U6.53 (GND), U7.5 (VSS), U8.1 (A0)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
/I2C_SCL: R18.2, U6.19 (IO5), U7.3 (SCL), U8.14 (SCL), U10.8 (SCL), U11.8 (SCL), U12.8 (SCL), U13.8 (SCL)
/I2C_SDA: R17.2, U6.18 (IO4), U7.4 (SDA), U8.15 (SDA), U10.7 (SDA), U11.7 (SDA), U12.7 (SDA), U13.7 (SDA)
/IO2: R12.2, U6.5 (IO2)
/ISO_INA: R1.2, U1.2 (INA)
/ISO_INB: R2.2, U1.3 (INB)
/LATCH_0V: U7.8 (EVI), U8.4 (P0), U16.5 (Q)
/LATCH_OV: U8.5 (P1), U16.9 (Q)
/LATCH_RST: R69.2, U6.21 (IO7), U16.1 (~R), U16.13 (~R)
/LED1_A: LED1.2 (A), R16.2
/LED2_A: LED2.2 (A), R22.2
/LED_ALM: LED2.1 (K), U8.11 (P6)
/LED_STAT: LED1.1 (K), R13.2, U6.22 (IO8)
/LSET_0V: R67.2, U14.1, U14.2, U14.13, U14.14, U15.1, U15.2, U16.4 (~S)
/LSET_OV: R68.2, U15.14, U16.10 (~S)
/MEAS_15BP: C30.1, R30.2, R40.1, U10.1 (CH1+), U15.8 (-)
/MEAS_BA1: C34.1, R34.2, R44.1, U11.1 (CH1+)
/MEAS_BA2: C35.1, R35.2, R45.1, U11.3 (CH2+)
/MEAS_BA3: C36.1, R36.2, R46.1, U11.11 (CH3+)
/MEAS_SIR: C57.1, R84.2, R85.1, U13.13 (CH4+)
/MEAS_SW1: C31.1, R31.2, R41.1, U10.3 (CH2+)
/MEAS_SW2: C32.1, R32.2, R42.1, U10.11 (CH3+)
/MEAS_SW3: C33.1, R33.2, R43.1, U10.13 (CH4+)
/MEAS_VBAT: C15.1, R9.2, R10.1, U11.13 (CH4+)
/PG_5V: R7.2, R8.1, U8.10 (P5)
/RTC_INT: R15.2, U6.16 (IO10), U7.2 (~INT)
/RTC_VB: C20.1, U7.6 (VBACKUP)
/SCL_BA1: J2.2, J3.2, JP1.4
/SCL_BA2: J4.2, J5.2, JP2.4
/SCL_BA3: J6.2, J7.2, JP3.4
/SCL_BP: J1.2, JP1.3, JP2.3, JP3.3, JP4.3
/SDA_BA1: J2.1, J3.1, JP1.2
/SDA_BA2: J4.1, J5.1, JP2.2
/SDA_BA3: J6.1, J7.1, JP3.2
/SDA_BP: J1.1, JP1.1, JP2.1, JP3.1, JP4.1
/SIREN_EN: R83.1, U6.20 (IO6), U17.4 (EN), U18.1 (IN)
/SIREN_P: D16.1 (A1), J11.3, R84.1, U18.3 (OUT)
/SNF_SCL: U1.6 (OUTB), U6.12 (IO0)
/SNF_SCL_J: JP4.4, R2.1
/SNF_SDA: U1.7 (OUTA), U6.13 (IO1)
/SNF_SDA_J: JP4.2, R1.1
/U0RX: J9.4, U6.30 (RXD0/IO20)
/U0TX: J9.3, U6.31 (TXD0/IO21)
/USB_DM: J9.7, U6.26 (IO18/USB_D-)
/USB_DP: J9.8, U6.27 (IO19/USB_D+)
/VBAT: C12.1, C56.1, F5.2, L2.1, Q1.3 (D), R9.1, U4.5 (BAT), U4.8 (FB), U17.5 (IN)
/VDIFF1: R60.2, U9.1, U13.1 (CH1+), U14.5 (+), U14.6 (-)
/VDIFF2: R61.2, U9.7, U13.3 (CH2+), U14.8 (-), U14.11 (+)
/VDIFF3: R62.2, U9.8, U13.11 (CH3+), U15.5 (+), U15.6 (-)
/VREF: R57.2, R58.2, R59.2, U9.13 (-), U9.14, U13.2 (CH1-), U13.4 (CH2-), U13.12 (CH3-)
/VREF_R: C41.1, R64.2, R65.1, U9.12 (+), U15.10 (-)
/VSYS: C10.1, C13.1, D6.1 (K), Q1.2 (S), U5.1 (VIN), U5.3 (EN)
/VTH_H: R63.2, R64.1, U14.7 (+), U14.9 (+), U15.7 (+), U15.9 (+)
/VTH_L: R65.2, R66.1, U14.4 (-), U14.10 (-), U15.4 (-)
/Z1_T: D11.1 (A1), J10.1, R71.1
/Z2_T: D12.1 (A1), J10.3, R72.1
/Z3_T: D13.1 (A1), J10.5, R73.1
/Z4_T: D14.1 (A1), J10.7, R74.1
/ZONE1_M: C51.1, R71.2, R75.2, U12.1 (CH1+)
/ZONE2_M: C52.1, R72.2, R76.2, U12.3 (CH2+)
/ZONE3_M: C53.1, R73.2, R77.2, U12.11 (CH3+)
/ZONE4_M: C54.1, R74.2, R78.2, U12.13 (CH4+)

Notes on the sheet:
ENTRÉE BP (J31) Brochage : 1 SDA, 2 SCL, 3 0 V, 4 +15 V
Queue de cochon AWG20 <= 15 cm soudée sur la broche traversante J31-3 du BP « 0 V TBTS – NE PAS RELIER À LA TERRE »
PORT BA1 : SC940D (J1 et J2 du BA)
PORT BA2 : SC941C (J1 et J2 du BA)
PORT BA3 : SC942C (J1 et J2 du BA)
N2 « étoile 0 V » – rév. B : carte d'étoile sur rail DIN + module ESP32 espion/alarme Partie bus (change i2c-surge-protection-2026-10-007, Refs #1) : SDA/SCL/+15 V/0 V du BP distribués vers chaque port BA ; par port : cavalier (SDA, SCL, +15 V), PTC puis TVS SMAJ16A. Le 0 V n'est jamais coupé et n'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
A – ÉCOUTE I2C PASSIVE : cavalier JP4, 1 kΩ série, isolateur unidirectionnel ISO7720 (2 canaux bus → module, aucun canal retour)
B – ALIMENTATION : PTC propre, anti-retour, TVS, abaisseur 15→5 V, chargeur LiFePO4 3,6 V 200 mA (CTN), power-path, LDO 3,3 V
C – MODULE ESP32-C3, RTC RV-3028 (supercondensateur), extension d'E/S TCA9534, débogage
D – MESURES : +15 V amont/aval des PTC (÷16), écart de 0 V (amplis différentiels G = 0,249), ADC MCP3428 x4
E – LATCH SURTENSION : fenêtre ±1 V sur l'écart de 0 V, +15 V > 20 V ; bascule 74HC74 réarmée par GPIO7
F – ALARME : 4 boucles équilibrées (FDL 2 x 4,7 kΩ), clé ARM, sirène 12 V (boost MT3608 + BTS4140N)

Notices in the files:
README.md:
Licence:
MIT, comme essensys-board-SC944D (voir `LICENSE`).
